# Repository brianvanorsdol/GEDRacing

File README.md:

# Objective: 
Provide a robust, highly modular grassroots-level Motorsport Development Board (MDB) along with a series of scalable peripherals

# Goals:
* Accuracy - Sensor readings can be trusted with as little noise as possible
* Reliability - alarms and triggers should initiate when needed
* Cost Effective - 
* Modular - 
* Familiar - Those with experience working with Arduino, ESP32, or other microcontrollers should feel familiar and be able to quickly get up to speed

# Key Features:
* ENTER SoC HERE****
  * ENTER CLOCK SPEED HERE****
* ENTER # OF GPIO HERE***
  * ENTER ANALOG PINS HERE***
  * ENTER DIGITAL PINS HERE***
* Programmable notification LED
* USB-C
* Two CANbus tranceivers to create an isolated CANbus from the vehicle and facilitate lightweight and familiar communication to a variety of peripherals
* External power/data distribution node 
* Rugged waterproof Deutsch enclosure
* Deutsch DTM connectors
* Removable storage

# Nice to Haves:
* Default Read-only mode - The MDB will always be set to a "read-only" mode for the CANbus connection to the vehicle to prevent accidental writing to the vehicle CANbus
* Data/CANbus backbone - A harness that originates at the external power/data distribution node and carries both the isolated CANbus (CAN H / CAN L) wires as well as 5v power
* External USB-C flashing - A USB cable that terminates at the main connector(s) to the MDB's enclosure and allows for flashing the MDB without removing it from its mounting position
* Hella sick wiring
* Transparent enclosure

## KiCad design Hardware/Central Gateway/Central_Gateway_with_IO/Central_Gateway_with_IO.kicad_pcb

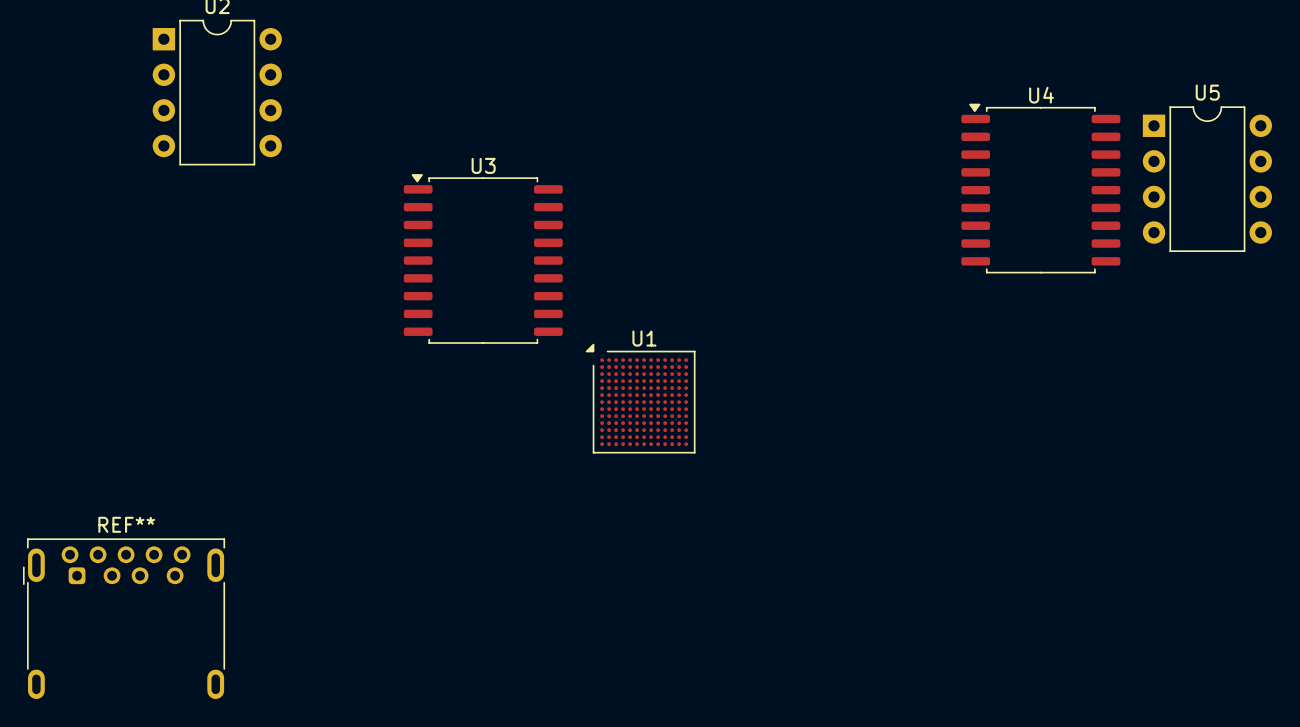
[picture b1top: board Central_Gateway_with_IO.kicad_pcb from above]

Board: 2 copper layers, 5 parts (0 on the bottom side), 8 nets, no tracks yet.

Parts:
U1: STM32H747AIIx; UFBGA-169_7x7mm_Layout13x13_P0.5mm
U2, U5: MCP2551-I-P; DIP-8_W7.62mm
U3, U4: MCP2515-xSO; SOIC-18W_7.5x11.6mm_P1.27mm

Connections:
GNDREF: U2.2 (VSS), U2.8 (Rs), U5.2 (VSS), U5.8 (Rs)
unnamed: U1.A1 (VSS), U1.A7 (VSS), U1.A12 (VSS), U1.B4 (VSS), U1.B9 (VSS), U1.C12 (VSS), U1.D1 (VSS), U1.E13 (VSS), U1.H2 (VSS), U1.H11 (VSS), U1.J11 (VSS), U1.K11 (VSS), U1.L13 (VSS), U1.M6 (VSS), U1.M9 (VSS), U1.N1 (VSS)
unnamed: U1.G12 (VSSDSI), U1.G13 (VSSDSI)
unnamed: U2.4 (RXD), U3.2 (RXCAN)
unnamed: U2.1 (TXD), U3.1 (TXCAN)
unnamed: U4.2 (RXCAN), U5.4 (RXD)
unnamed: U4.1 (TXCAN), U5.1 (TXD)
VCC: U2.3 (VDD), U3.18 (VDD), U4.18 (VDD), U5.3 (VDD)

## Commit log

2024-11-02 Create Pull Test
2024-11-03 check
2024-11-03 Added Hardware directory for Central Gateway PCB CAD Models
2024-11-03 Directory for Libraries and applications?
2024-11-03 Empty project commit
2024-11-03 Create README.md
    Added Overall Objective, Goals, Key Features, and Nice to Haves
2024-11-03 Added various folders for Doodads
2024-11-22 Began KiCAD schematic
    Added following items to schematic:
    STM32h747
    2x MCP 2551
    2x MCP 2515
    2x Crystal Oscillator
    4x Capacitors
2024-11-22 Added current code for shift lights
    Current prototype code for shift lights. Works as of now and has the following features:
    -Brightness control
    -Start LED on at 3k RPM, 500 RPM increments, 6700 RPM flash point
2025-01-10 Uploading initial working software for A90 Supra Shift Lights. Includes following functionality: 1. BLE control via the RemoteXY app (brightness, on/off, shift point, rpm increment, rpm startpoint) 2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
2025-01-12 Added folder to hold wiring diagram elements as well as a PNG wiring diagram showing the basic wiring of the shift ligths
2025-01-12 Deleted Placeholder.txt
2025-01-13 Deleted older versions, renamed current working version
2025-01-14 Updated CAN TX and RX pin as well as commented out a few debug outputs
